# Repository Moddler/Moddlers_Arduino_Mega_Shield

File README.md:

# Moddlers_Arduino_Mega_Shield
A generic Arduino Mega Shield template for KiCad

For some reason I did not realize a template existed in KiCAD, so I created one. Here it is.

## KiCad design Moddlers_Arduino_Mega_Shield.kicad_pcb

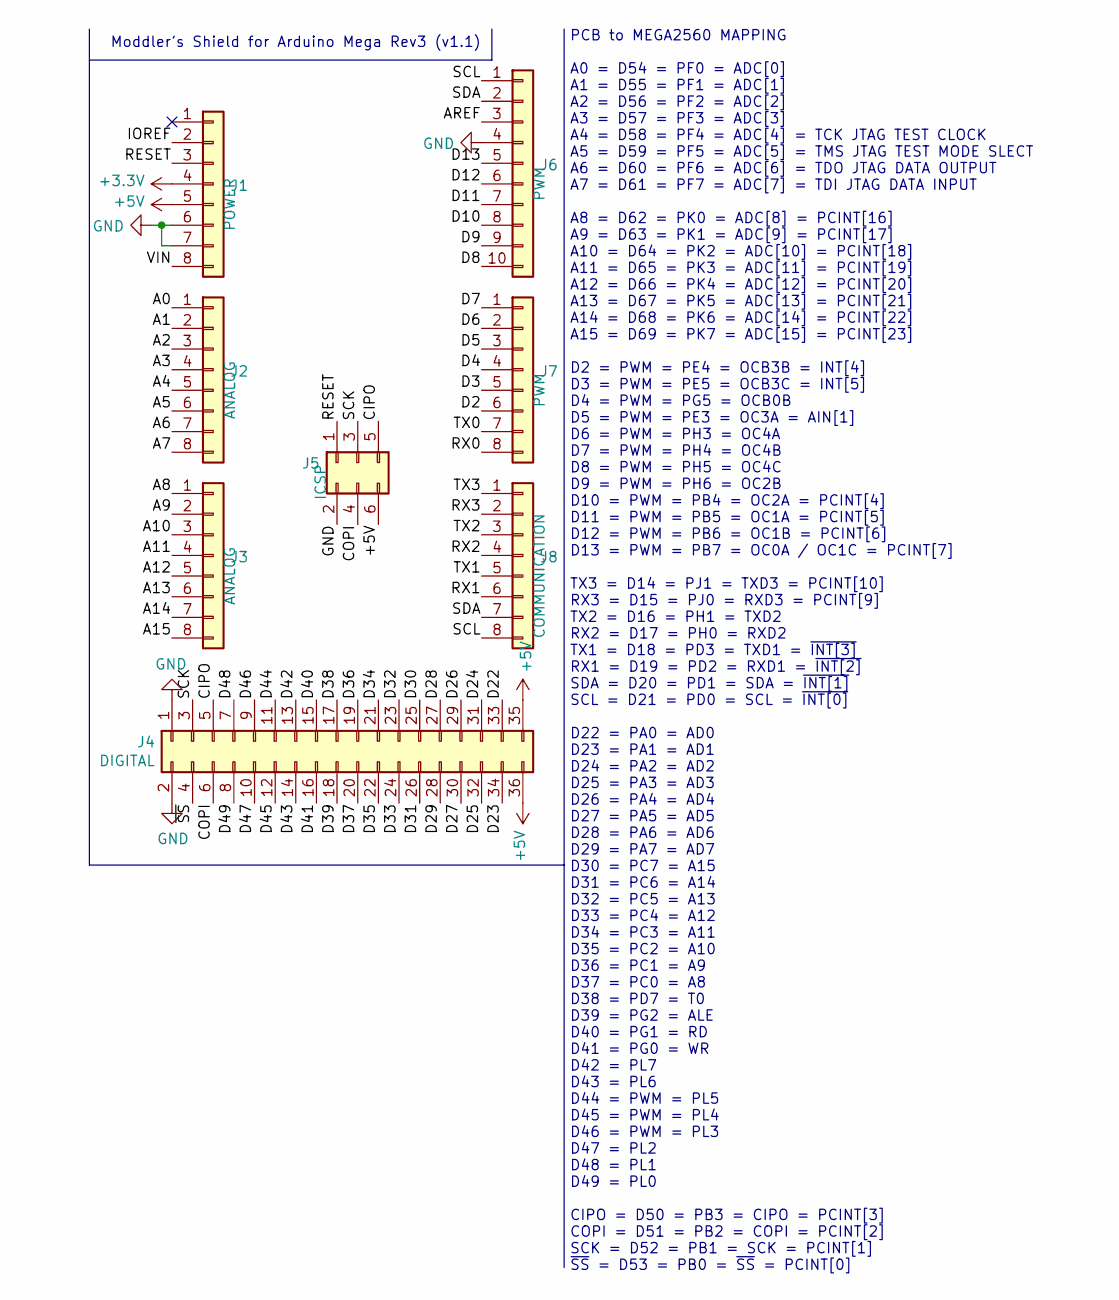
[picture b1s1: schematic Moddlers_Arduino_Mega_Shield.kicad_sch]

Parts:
J1: POWER; PinHeader_1x08_P2.54mm_Vertical
J2, J3: ANALOG; PinHeader_1x08_P2.54mm_Vertical
J4: DIGITAL; PinHeader_2x18_P2.54mm_Vertical
J5: ICSP; PinHeader_2x03_P2.54mm_Vertical
J6: PWM; PinHeader_1x10_P2.54mm_Vertical
J7: PWM; PinHeader_1x08_P2.54mm_Vertical
J8: COMMUNICATION; PinHeader_1x08_P2.54mm_Vertical

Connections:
+3V3: J1.4
+5V: J1.5, J4.35, J4.36, J5.6
/A0: J2.1
/A1: J2.2
/A2: J2.3
/A3: J2.4
/A4: J2.5
/A5: J2.6
/A6: J2.7
/A7: J2.8
/A8: J3.1
/A9: J3.2
/A10: J3.3
/A11: J3.4
/A12: J3.5
/A13: J3.6
/A14: J3.7
/A15: J3.8
/AREF: J6.3
/CIPO: J4.5, J5.5
/COPI: J4.6, J5.4
/D2: J7.6
/D3: J7.5
/D4: J7.4
/D5: J7.3
/D6: J7.2
/D7: J7.1
/D8: J6.10
/D9: J6.9
/D10: J6.8
/D11: J6.7
/D12: J6.6
/D13: J6.5
/D22: J4.33
/D23: J4.34
/D24: J4.31
/D25: J4.32
/D26: J4.29
/D27: J4.30
/D28: J4.27
/D29: J4.28
/D30: J4.25
/D31: J4.26
/D32: J4.23
/D33: J4.24
/D34: J4.21
/D35: J4.22
/D36: J4.19
/D37: J4.20
/D38: J4.17
/D39: J4.18
/D40: J4.15
/D41: J4.16
/D42: J4.13
/D43: J4.14
/D44: J4.11
/D45: J4.12
/D46: J4.9
/D47: J4.10
/D48: J4.7
/D49: J4.8
/IOREF: J1.2
/RESET: J1.3, J5.1
/RX0: J7.8
/RX1: J8.6
/RX2: J8.4
/RX3: J8.2
/SCK: J4.3, J5.3
/SCL: J6.1, J8.8
/SDA: J6.2, J8.7
/TX0: J7.7
/TX1: J8.5
/TX2: J8.3
/TX3: J8.1
/VIN: J1.8
/~SS: J4.4
GND: J1.6, J1.7, J4.1, J4.2, J5.2, J6.4

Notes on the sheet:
PCB to MEGA2560 MAPPING A0 = D54 = PF0 = ADC[0] A1 = D55 = PF1 = ADC[1] A2 = D56 = PF2 = ADC[2] A3 = D57 = PF3 = ADC[3] A4 = D58 = PF4 = ADC[4] = TCK JTAG TEST CLOCK A5 = D59 = PF5 = ADC[5] = TMS JTAG TEST MODE SLECT A6 = D60 = PF6 = ADC[6] = TDO JTAG DATA OUTPUT A7 = D61 = PF7 = ADC[7] = TDI JTAG 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
Moddler’s Shield for Arduino Mega Rev3 (v1.1)

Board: 2 copper layers, 8 parts (8 on the bottom side), 8 nets, no tracks yet.

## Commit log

2022-01-09 upload version 1.1
2022-01-31 Update to KiCAD Version 6, add missing INT mapping, Error-Correction

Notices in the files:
Moddlers_Arduino_Mega_Shield.kicad_pcb:
(c) 2022 Moddler
